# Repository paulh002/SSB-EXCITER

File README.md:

# SSB-EXCITER
A SSB exciter board, contains a AF amplifier, balanced modulater, and mixer and driver.
The driver is based on BFG135a. The amplifier stages after xtal filter are based on ubitx design.

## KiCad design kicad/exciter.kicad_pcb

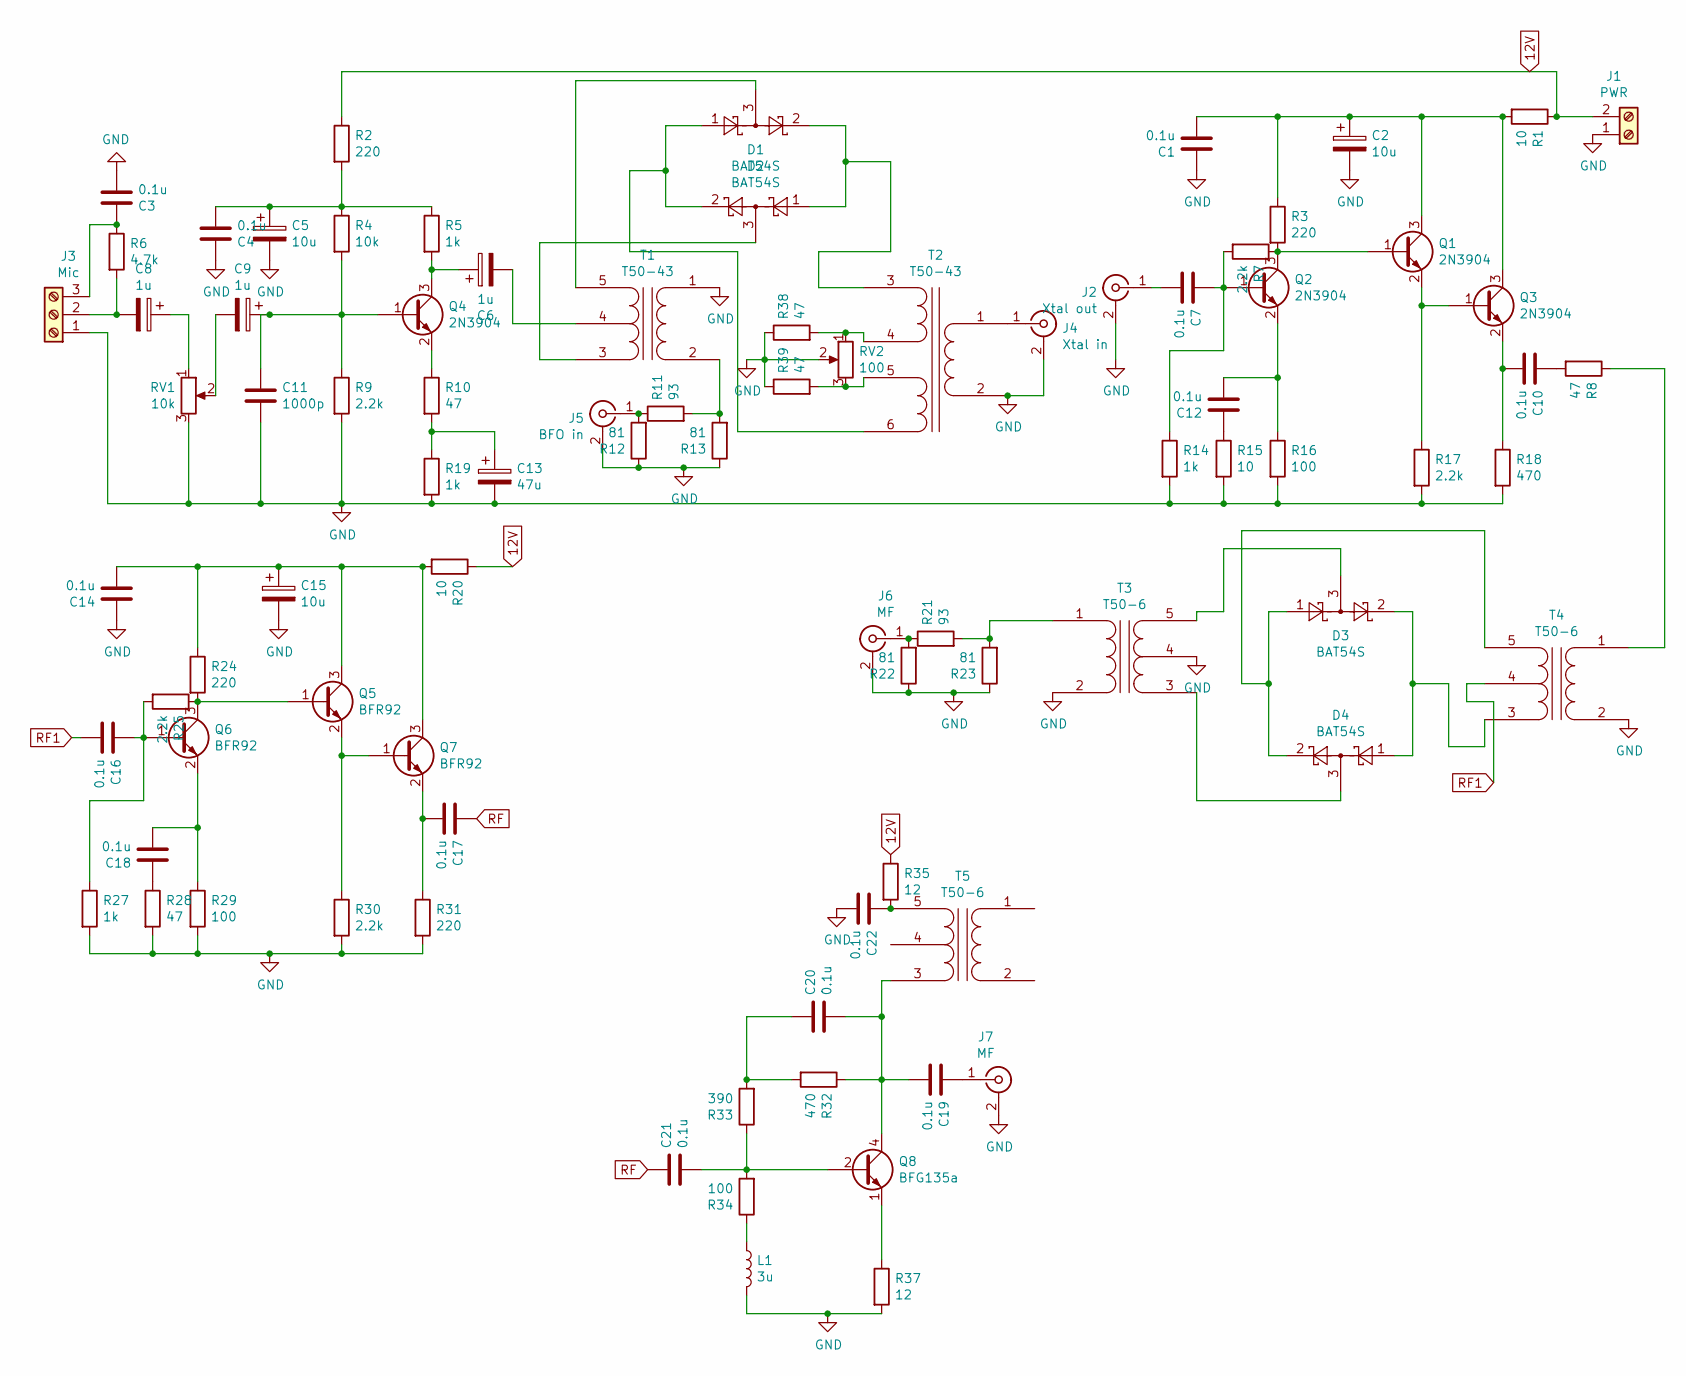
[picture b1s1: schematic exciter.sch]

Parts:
C1, C3, C4, C7, C10, C12, C14, C16, C17, C18, C19, C20, C21, C22: 0.1u; C_1206_3216Metric_Pad1.42x1.75mm_HandSolder
C2, C5, C15: 10u; C_1206_3216Metric_Pad1.42x1.75mm_HandSolder
C6, C8, C9: 1u; CP_Radial_D4.0mm_P2.00mm
C11: 1000p; C_1206_3216Metric_Pad1.42x1.75mm_HandSolder
C13: 47u; CP_Radial_D6.3mm_P2.50mm
D1, D2, D3, D4: BAT54S; SOT-23
J1: PWR; TerminalBlock_MetzConnect_Type055_RT01502HDWU_1x02_P5.00mm_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
J2: Xtal out; SMA_Amphenol_132134_Vertical
J3: Mic; TerminalBlock_MetzConnect_Type055_RT01503HDWU_1x03_P5.00mm_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
J4: Xtal in; SMA_Amphenol_132134_Vertical
J5: BFO in; SMA_Amphenol_132134_Vertical
J6, J7: MF; SMA_Amphenol_132134_Vertical
L1: 3u; L_Bourns-SRN4018
Q1, Q2, Q3, Q4: 2N3904; SOT-23
Q5, Q6, Q7: BFR92; SOT-23
Q8: BFG135a; SOT-223
R1, R15, R20: 10; R_1206_3216Metric_Pad1.42x1.75mm_HandSolder
R2, R3, R24, R31: 220; R_1206_3216Metric_Pad1.42x1.75mm_HandSolder
R4: 10k; R_1206_3216Metric_Pad1.42x1.75mm_HandSolder
R5, R14, R19, R27: 1k; R_1206_3216Metric_Pad1.42x1.75mm_HandSolder
R6: 4.7k; R_1206_3216Metric_Pad1.42x1.75mm_HandSolder
R7, R9, R17, R25, R30: 2.2k; R_1206_3216Metric_Pad1.42x1.75mm_HandSolder
R8, R10, R28, R38, R39: 47; R_1206_3216Metric_Pad1.42x1.75mm_HandSolder
R11, R21: 93; R_1206_3216Metric_Pad1.42x1.75mm_HandSolder
R12, R13, R22, R23: 81; R_1206_3216Metric_Pad1.42x1.75mm_HandSolder
R16, R29, R34: 100; R_1206_3216Metric_Pad1.42x1.75mm_HandSolder
R18, R32: 470; R_1206_3216Metric_Pad1.42x1.75mm_HandSolder
R33: 390; R_1206_3216Metric_Pad1.42x1.75mm_HandSolder
R35, R37: 12; R_1206_3216Metric_Pad1.42x1.75mm_HandSolder
RV1: 10k; Potentiometer_ACP_CA9-H2,5_Horizontal
RV2: 100; Potentiometer_Bourns_3296W_Vertical
T1: T50-43; Transformer_Toroid_Horizontal_3S_D14.0mm_Amidon-T50
T2: T50-43; Transformer_Toroid_Horizontal_4S_D14.0mm_Amidon-T50
T3, T4, T5: T50-6; Transformer_Toroid_Horizontal_3S_D14.0mm_Amidon-T50

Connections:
12V: J1.2, R1.1, R2.1, R20.1, R35.1
GND: C1.1, C2.2, C3.2, C4.1, C5.2, C11.2, C13.2, C14.1, C15.2, C22.2, J1.1, J2.2 (Ext), J3.1, J4.2 (Ext), J5.2 (Ext), J6.2 (Ext), J7.2 (Ext), L1.2, R9.2, R12.1, R13.1, R14.2, R15.2, R16.2, R17.2, R18.2, R19.2, R22.1, R23.1, R27.2, R28.2, R29.2, R30.2, R31.2, R37.2, R38.1, R39.1, RV1.3, RV2.2, T1.1 (AA), T2.2 (AB), T3.2 (AB), T3.4 (SC), T4.2 (AB)
unnamed: C1.2, C2.1, Q1.3 (C), Q3.3 (C), R1.2, R3.1
unnamed: C3.1, J3.3, R6.1
unnamed: C4.2, C5.1, R2.2, R4.1, R5.1
unnamed: C6.1, Q4.3 (C), R5.2
unnamed: C6.2, T1.4 (SC)
unnamed: C7.1, Q2.1 (B), R7.2, R14.1
unnamed: C7.2, J2.1 (In)
unnamed: C8.1, RV1.1
unnamed: C8.2, J3.2, R6.2
unnamed: C9.2, RV1.2
unnamed: C10.1, R8.2
unnamed: C10.2, Q3.2 (E), R18.1
unnamed: C9.1, C11.1, Q4.1 (B), R4.2, R9.1
unnamed: C12.1, R15.1
unnamed: C12.2, Q2.2 (E), R16.1
unnamed: C13.1, R10.2, R19.1
unnamed: C14.2, C15.1, Q5.3 (C), Q7.3 (C), R20.2, R24.1
unnamed: C16.1, Q6.1 (B), R25.2, R27.1
unnamed: C17.2, Q7.2 (E), R31.1
unnamed: C18.1, R28.1
unnamed: C18.2, Q6.2 (E), R29.1
unnamed: C19.1, J7.1 (In)
unnamed: C19.2, C20.2, Q8.4 (C), R32.1, T5.3 (SA)
unnamed: C20.1, R32.2, R33.2
unnamed: C21.2, Q8.2 (B), R33.1, R34.2
unnamed: C22.1, R35.2, T5.5 (SB)
unnamed: D1.1, D2.2, T2.6 (SD)
unnamed: D1.2, D2.1, T2.3 (SA)
unnamed: D1.3, T1.5 (SB)
unnamed: D2.3, T1.3 (SA)
unnamed: D3.1, D4.2, T4.5 (SB)
unnamed: D3.2, D4.1, T4.3 (SA)
unnamed: D3.3, T3.5 (SB)
unnamed: D4.3, T3.3 (SA)
unnamed: J4.1 (In), T2.1 (AA)
unnamed: J5.1 (In), R11.1, R12.2
unnamed: J6.1 (In), R21.1, R22.2
unnamed: L1.1, R34.1
unnamed: Q1.1 (B), Q2.3 (C), R3.2, R7.1
unnamed: Q1.2 (E), Q3.1 (B), R17.1
unnamed: Q4.2 (E), R10.1
unnamed: Q5.1 (B), Q6.3 (C), R24.2, R25.1
unnamed: Q5.2 (E), Q7.1 (B), R30.1
unnamed: Q8.1 (E), Q8.3 (E), R37.1
unnamed: R8.1, T4.1 (AA)
unnamed: R11.2, R13.2, T1.2 (AB)
unnamed: R21.2, R23.2, T3.1 (AA)
unnamed: R38.2, RV2.1, T2.4 (SB)
unnamed: R39.2, RV2.3, T2.5 (SC)
RF: C17.1, C21.1
RF1: C16.2, T4.4 (SC)

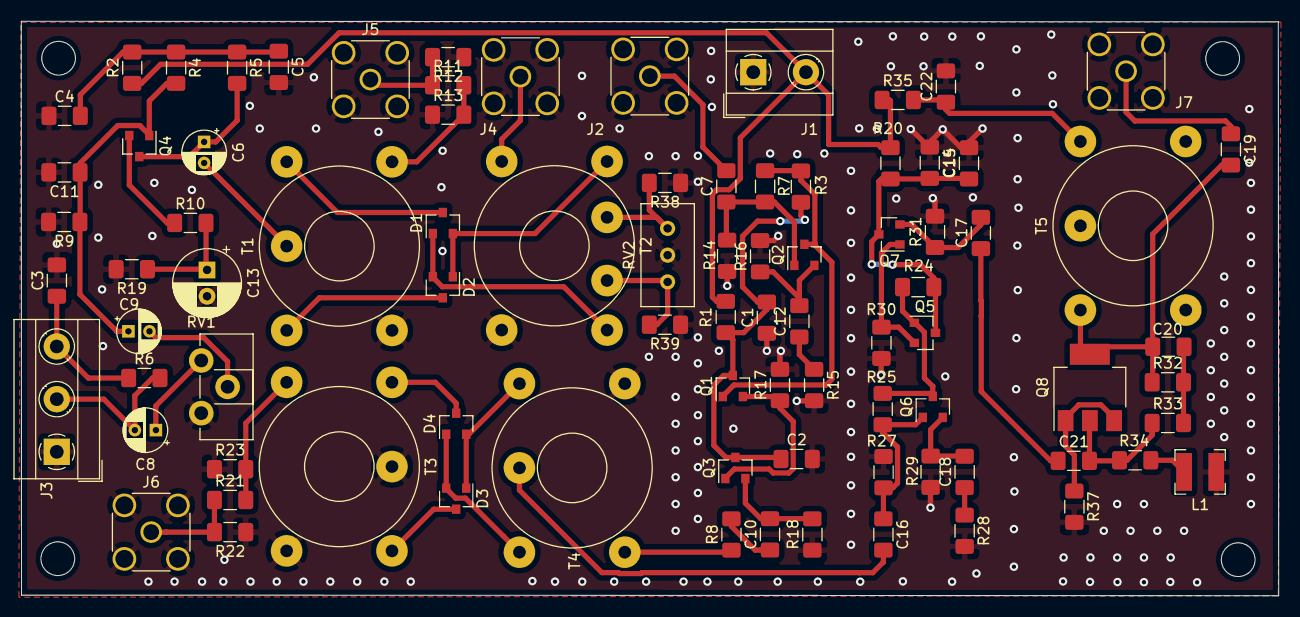
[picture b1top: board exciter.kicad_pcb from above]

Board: 2 copper layers, 119.3 x 54.5 mm, 90 parts (0 on the bottom side), 53 nets.

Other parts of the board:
 : MountingHole_3.2mm_M3
 #2,  #3,  #4: MountingHole_3.2mm_M3
